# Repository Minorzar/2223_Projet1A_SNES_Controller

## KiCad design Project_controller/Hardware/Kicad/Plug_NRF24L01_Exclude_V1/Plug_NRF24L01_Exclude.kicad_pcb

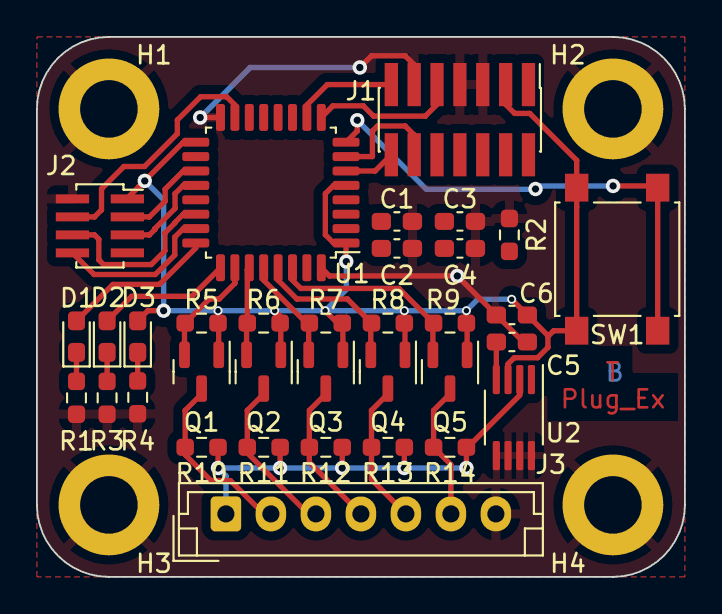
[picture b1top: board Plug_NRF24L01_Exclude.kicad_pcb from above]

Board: 2 copper layers, 36.0 x 30.0 mm, 38 parts (0 on the bottom side), 30 nets.

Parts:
C1, C2, C3, C4: 100n; C_0603_1608Metric_Pad1.08x0.95mm_HandSolder
C5: 470p; C_0603_1608Metric_Pad1.08x0.95mm_HandSolder
C6: 2.2u; C_0603_1608Metric_Pad1.08x0.95mm_HandSolder
D1, D2: LED_Small; D_0603_1608Metric_Pad1.05x0.95mm_HandSolder
D3: LED; D_0603_1608Metric_Pad1.05x0.95mm_HandSolder
H1, H2, H3, H4: MountingHole_Pad; MountingHole_3.2mm_M3_DIN965_Pad
J1: Conn_02x07_Odd_Even; PinHeader_2x07_P1.27mm_Vertical_SMD
J2: Conn_01x08_Socket; PinSocket_2x04_P1.00mm_Vertical_SMD
J3: Conn_01x07_Socket; JST_EH_B7B-EH-A_1x07_P2.50mm_Vertical
Q1, Q2, Q3, Q4, Q5: 2N7002; SOT-23
R1, R3, R4: 1k; R_0603_1608Metric_Pad0.98x0.95mm_HandSolder
R2, R5, R6, R7, R8, R9, R10, R11, R12, R13, R14: 10k; R_0603_1608Metric_Pad0.98x0.95mm_HandSolder
SW1: SW_SPST; SW_SPST_B3S-1000
U1: STM32L412KBTx; LQFP-32_7x7mm_P0.8mm
U2: MIC5219-3.3YMM; MSOP-8_3x3mm_P0.65mm

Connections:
+3.3V: C2.1, C3.1, C4.1, C6.1, D3.2 (A), J1.3, J2.1, Q1.1 (G), Q2.1 (G), Q3.1 (G), Q4.1 (G), Q5.1 (G), R5.1, R6.1, R7.1, R8.1, R9.1, SW1.2 (B), U1.1 (VDD), U1.5 (VDDA), U1.17 (VDD), U2.3 (OUT)
+5V: J3.1, R10.1, R11.1, R12.1, R13.1, R14.1, U2.2 (IN)
Appairing_Btn: R2.1, SW1.1 (A), U1.8 (PA2)
Chip_Enable: J2.4, U1.15 (PB1)
Data_Clock_SNES: J3.2, Q1.3 (D), R10.2
Data_Clock_STM32: Q1.2 (S), R5.2, U1.26 (PB3)
Data_Latch_SNES: J3.3, Q2.3 (D), R11.2
Data_Latch_STM32: Q2.2 (S), R6.2, U1.27 (PB4)
GND: C1.1, C2.2, C3.2, C4.2, C5.2, C6.2, H1.1, H2.1, H3.1, H4.1, J1.5, J1.7, J1.11, J2.2, J3.7, R1.2, R2.2, R3.2, R4.2, U1.16 (VSS), U1.32 (VSS), U2.5 (GND), U2.6 (GND), U2.7 (GND), U2.8 (GND)
IOBit_SNES: J3.6, Q5.3 (D), R14.2
IOBit_STM32: Q5.2 (S), R9.2, U1.30 (PB7)
NRST: C1.2, J1.10, U1.4 (NRST)
unnamed: D1.1 (K), R1.1
unnamed: D2.1 (K), R3.1
unnamed: D3.1 (K), R4.1
unnamed: C5.1, U2.4 (BP)
Player1_LED: D1.2 (A), U1.24 (PA14)
SPI_Chip_Select: J2.3, U1.19 (PA9)
SPI_Clock: J2.6, U1.22 (PA12)
SPI_Digital_Input: J2.5, U1.20 (PA10)
SPI_Digital_Output: J2.8, U1.23 (PA13)
SWDCK: J1.13, U1.10 (PA4)
SWDIO: J1.9, U1.9 (PA3)
Serial_Data1_SNES: J3.4, Q3.3 (D), R12.2
Serial_Data1_STM32: Q3.2 (S), R7.2, U1.28 (PB5)
Serial_Data2_SNES: J3.5, Q4.3 (D), R13.2
Serial_Data2_STM32: Q4.2 (S), R8.2, U1.29 (PB6)
Status_LED: D2.2 (A), U1.25 (PA15)
USART2_RX: J1.12, U1.7 (PA1)
USART2_TX: J1.14, U1.6 (PA0)
